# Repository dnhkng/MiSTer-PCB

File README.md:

# MiSTer-PCB

# A DIY low-profile case for the MiSTer Project!

Build a nice, minimal case that works very well with 8bitdo sega controllers.  When it's finished, you'll have a case with just a single power cables, and a custom short OTG USB cable fo a very tidy setup.

## Parts List
For this project you will need:
- 1x DE10 Nano
- 1x Arduino Pro Micro
- 2 PCB's, the designs and schematics are in this repo
- 4x M3 16mm bolts
- 4x M3 nuts
- 2x 3D printed side panels or 8x M3 nuts
- 3x 12mm buttons
- single-row pin header, male and female
- 2x 8BitDo M30 2.4G wireless controllers
- 40mm 5V fan (optional)
- heatsink (optional)
- SDRAM (optional)

# Flashing the Arduino
Grabe the code from this Repo:
https://github.com/MickGyver/DaemonBite-Retro-Controllers-USB

**NOTE! Make sure you use the code from the SegaTwoControllersUSB Folder**

Use the latest Arduino GUI to flash the Arduino Pro Micro via USB. This can also be done after the board is assembled.

# Building the Case

You need to get some PCB's made. In this repo are the Eagle board files. I had black PCB's with lead-free HASL, which gives you a nice black/silver loof for the logo. You also need to 3D print the side panels, I used black PLA to match the PCB's.

Then, on to assembly!

## Soldering the parts
Get all the parts ready, and some lead-free solder. As the solder joints are a bit exposed in the end, you don't want exposed lead!

### Start with the Arduino Pro Micro

 - The Arduino is soldering on with single-side pads, so there's no ugly solder joints on the top surface.
 - Melt the solder through the holes until you see the solder leak through onto the pads.
 - The pin-headers for the 8BitDo 2.4G adapters can be soldered next. Cut your pin headers to 2x 4 pin and 2x 5 pin strips, and solder the short ends from the top of the cover.
 - attach a 5V 40mm fan (optional), then cut the wires to length and solder to the top case PCB.

 - the buttons pop-in from the top, and the kink in the legs hold them in place while you solder.

 - The hardest part in the whole project is the DE10 Nano heard connector. Cut a Female pin header up, and solder it in place as shown.

## Assembly

Now its time to put the parts together! You can see the order of the parts in the next picture. First, take off the brass risers from the DE10 Nano, we'll need them soon.
 - Add the SDRAM to the DE10 Nano
 - Push the M3 16mm bolts through the base plate, the 3D printed sides, the DE10 nano, and into the brass risers.
 - Don't forget to either make a hole in one for the SD card, or insert the SD card now.

**If you don't have the 3D printed side panels, you can use 2x M3 nuts per M3 bolt as a spacer between the bottom panel and the DE10 Nano!**

 - Then align the header connectors on the top case with the DE10 Nano, and carefullt push everything together.
 - Finally, use the M3 nuts on the brass riser srew to hold everything together.

 - You can then push the 8Bitdo adapters on to the pin headers

Once the assemlby is done, you can either use a OTG Hub, and connect the hub to the Arduino, or you can also make a short USB Micro cable to keep things tidy. I used a black marker to 'paint' the SDRAM module PCB black, and make everything look more professional.

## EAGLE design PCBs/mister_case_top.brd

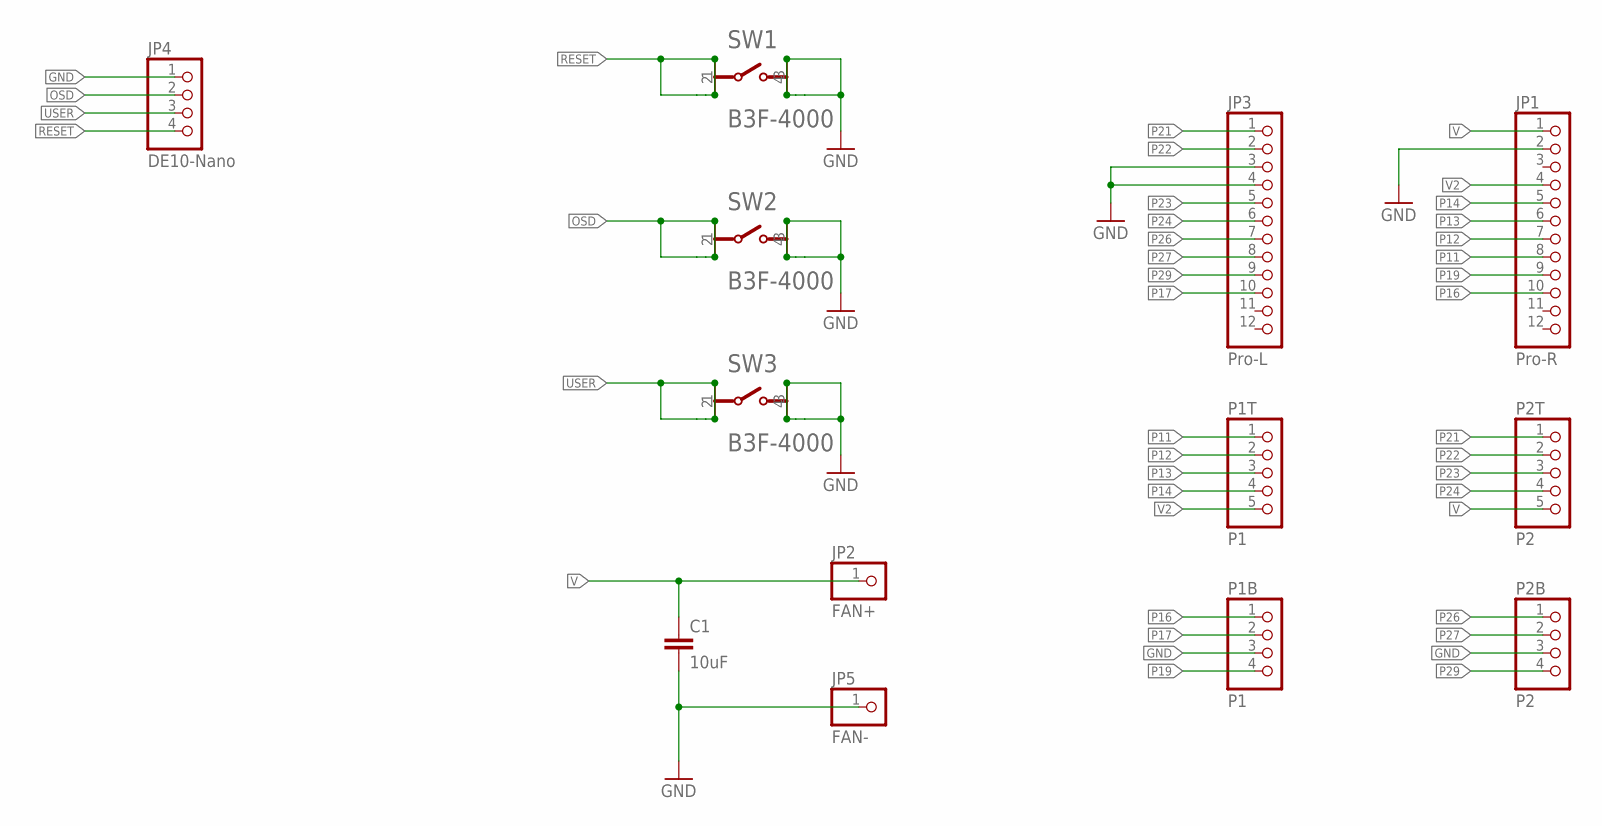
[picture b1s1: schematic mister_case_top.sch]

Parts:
C1: 10uF; C0805
JP1: Pro-R; 1X12L-NOHOLES
JP2: FAN+; 1X01
JP3: Pro-L; 1X12L-NOHOLES
JP4: DE10-Nano; 1X04
JP5: FAN-; 1X01
P1B: P1; 1X04
P1T: P1; 1X05
P2B: P2; 1X04
P2T: P2; 1X05
SW1, SW2, SW3: OMRON_B3F-4000; OMRON_B3F-4000_NOHOLES

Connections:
GND: C1.2, JP1.2, JP3.3, JP3.4, JP4.1, JP5.1, P1B.3, P2B.3, SW1.3, SW1.4, SW2.3, SW2.4, SW3.3, SW3.4
OSD: JP4.2, SW2.1, SW2.2
P11: JP1.8, P1T.1
P12: JP1.7, P1T.2
P13: JP1.6, P1T.3
P14: JP1.5, P1T.4
P16: JP1.10, P1B.1
P17: JP3.10, P1B.2
P19: JP1.9, P1B.4
P21: JP3.1, P2T.1
P22: JP3.2, P2T.2
P23: JP3.5, P2T.3
P24: JP3.6, P2T.4
P26: JP3.7, P2B.1
P27: JP3.8, P2B.2
P29: JP3.9, P2B.4
RESET: JP4.4, SW1.1, SW1.2
USER: JP4.3, SW3.1, SW3.2
V: C1.1, JP1.1, JP2.1, P2T.5
V2: JP1.4, P1T.5

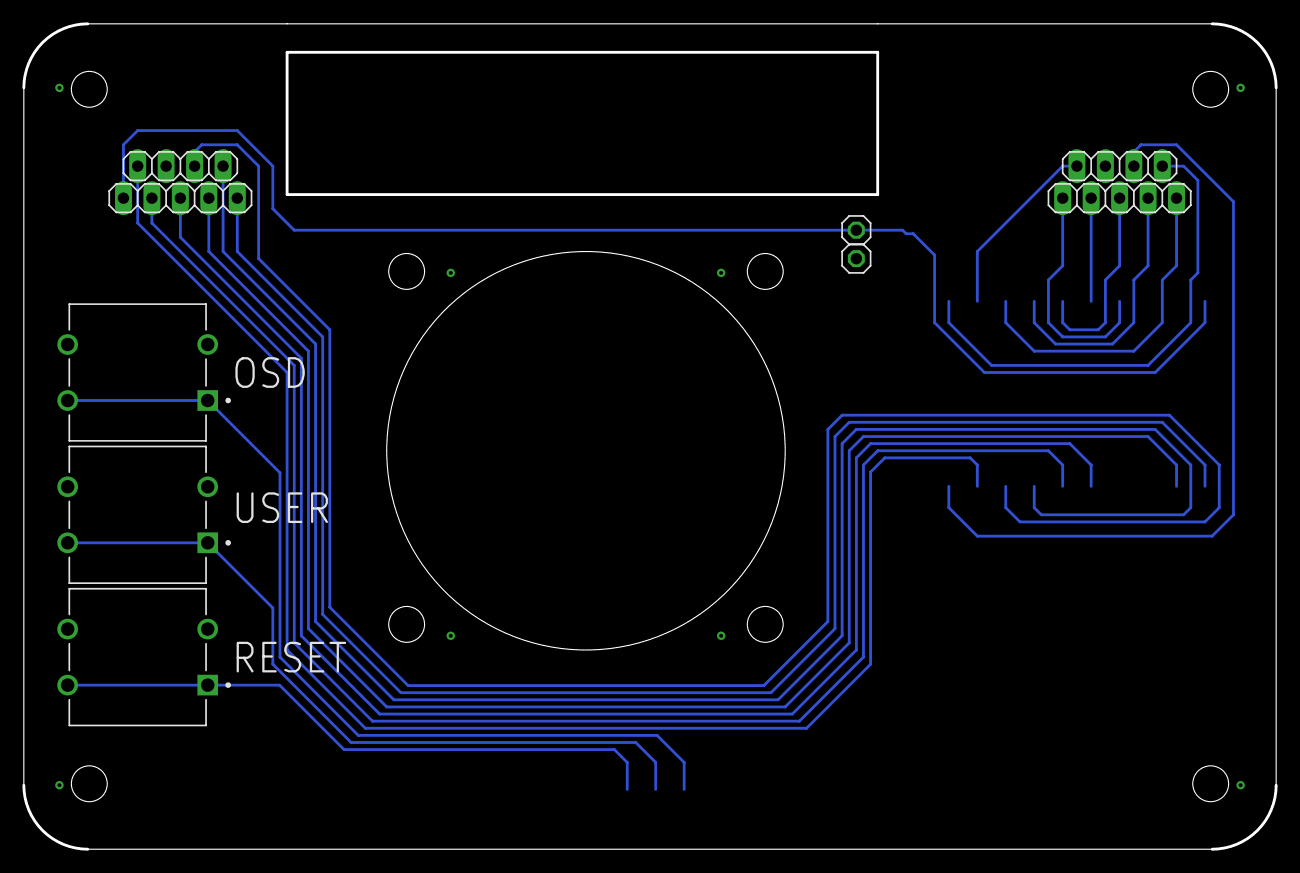
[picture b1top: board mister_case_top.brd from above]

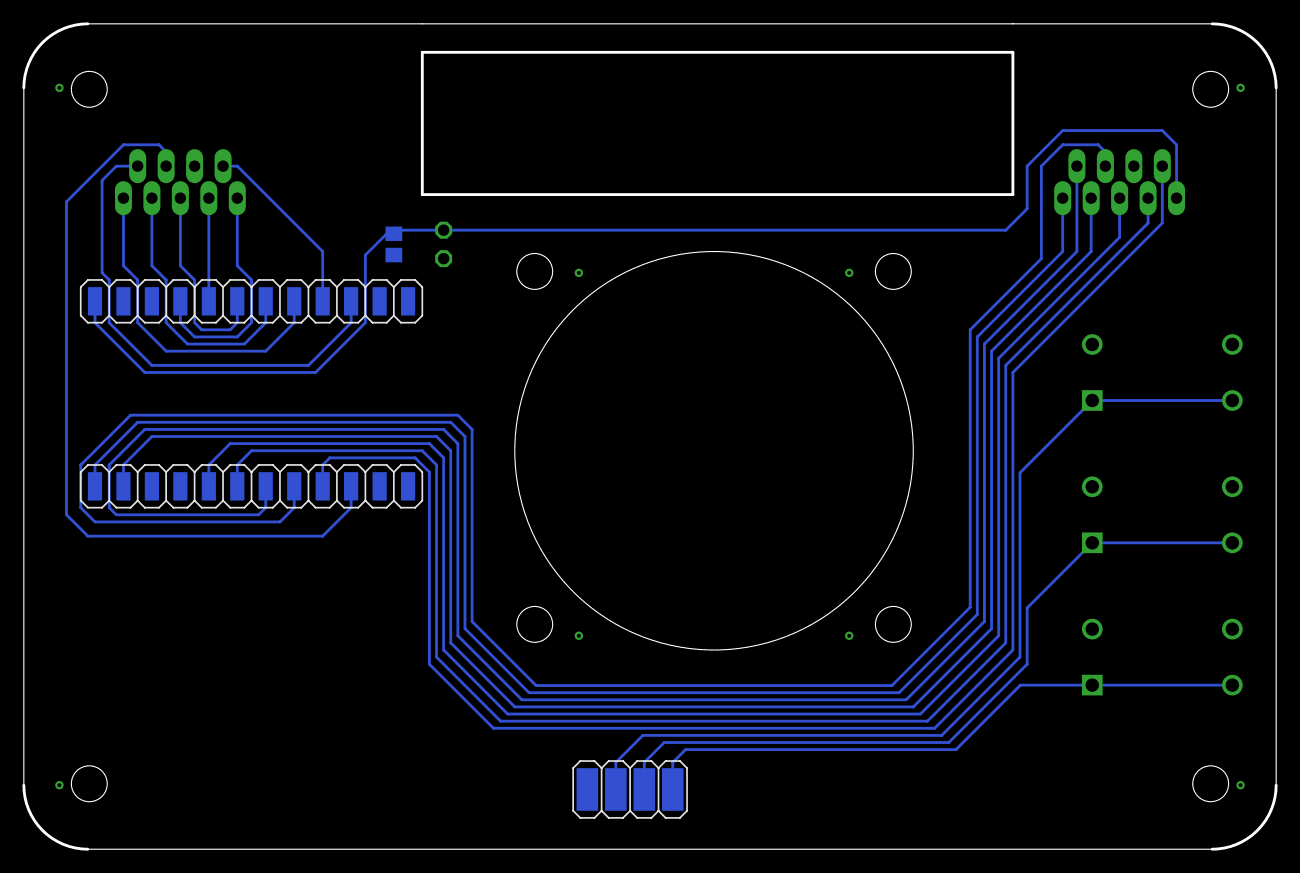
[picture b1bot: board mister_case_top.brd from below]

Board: 2 copper layers, 111.8 x 73.7 mm, 13 parts (4 on the bottom side), 20 nets.

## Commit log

2021-05-25 Image upload
2021-05-25 name fix
2021-07-16 Update construction guide
2021-07-16 Spelling
